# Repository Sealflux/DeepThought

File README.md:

# DeepThought
A pocket keychain that displays DeepSeek quotes on an OLED at the push of a button. 
Powered by a Seeed XIAO ESP32-C3
## Built for Horizons Polaris Hack Club
## Features
- Press button to cycle through DeepSeek quotes
- 128x64 OLED Display
- Compact keychain(slay!!)
- Rechargable LiPo Battery

## Hardware
- Seeed Xiao ESP32-C3
- SSD1306 128x64 OLED (I2C)
- Tactile Push Button
- 250mAh LiPo Battery
- 3D-printed case

## BOM
| Part | Quantity | Cost | Link
|------|-----|------|------|
| Seeed Xiao ESP32-C3 | 1 | $6.35 | https://www.seeedstudio.com/Seeed-XIAO-ESP32C3-p-5431.html |
| SSD1306 0.96" OLED | 1 | $2.24 | https://www.lcsc.com/product-detail/C5248080.html |
| Tactile Push Button | 50 | $0.56 | https://www.lcsc.com/product-detail/C2888493.html |
| LiPo 250mAh | 1 | $9.95 | https://www.amazon.com/EEMB-Battery-Rechargeable-Lithium-Connector/dp/B08FD3V6TF |
| PCB Board | 5 | $2.10 | https://www.jlcpcb.com | 
| Shipping | 1 | $52.39 | $6.20(Seeed) + $11.33(LCSC) + $6.99(Amazon) + $27.87(JLCPCB) |

## Steps To Reproduce

1. Order PCB from JLCPCB, uploading the gerbers.zip in the production folder.
2. 3D print the case using the Bottom and Top stl in the production folder.
3. Order parts using the BOM links above.
4. Solder the parts from the BOM links above to the PCB.
5. Connect the LiPo battery to the battery pads of the PCB(its at the top)
6. Flash the firmware using Arduino IDE in the firmware folder.
7. Assemble the case using super glue, sand down the edges first for better connection.
8. Use Deepthought by pressing the button!

## Firmware/Programming
### Steps to connect/use replicate/mirror the official Seeed website: https://wiki.seeedstudio.com XIAO_ESP32C3_Getting_Started/

1. Connect XIAO ESP32C3 to your computer via a USB Type-C cable.
2. Donwload and Install Arduino IDE
3. Add ESP32 board package to your Arduino IDE
4. Intall Adafruit SSD1306 and Adafruit GFX libraries
5. Download the code from the firmware folder and open it or copy and paste it into the IDE!
5. Select the board
6. Upload the code

## Schematic

## PCB

## PCBA

## Case

## Photos of real thing if I actually can afford grant from horizons(probably not, please polaris!)

## Demo Video

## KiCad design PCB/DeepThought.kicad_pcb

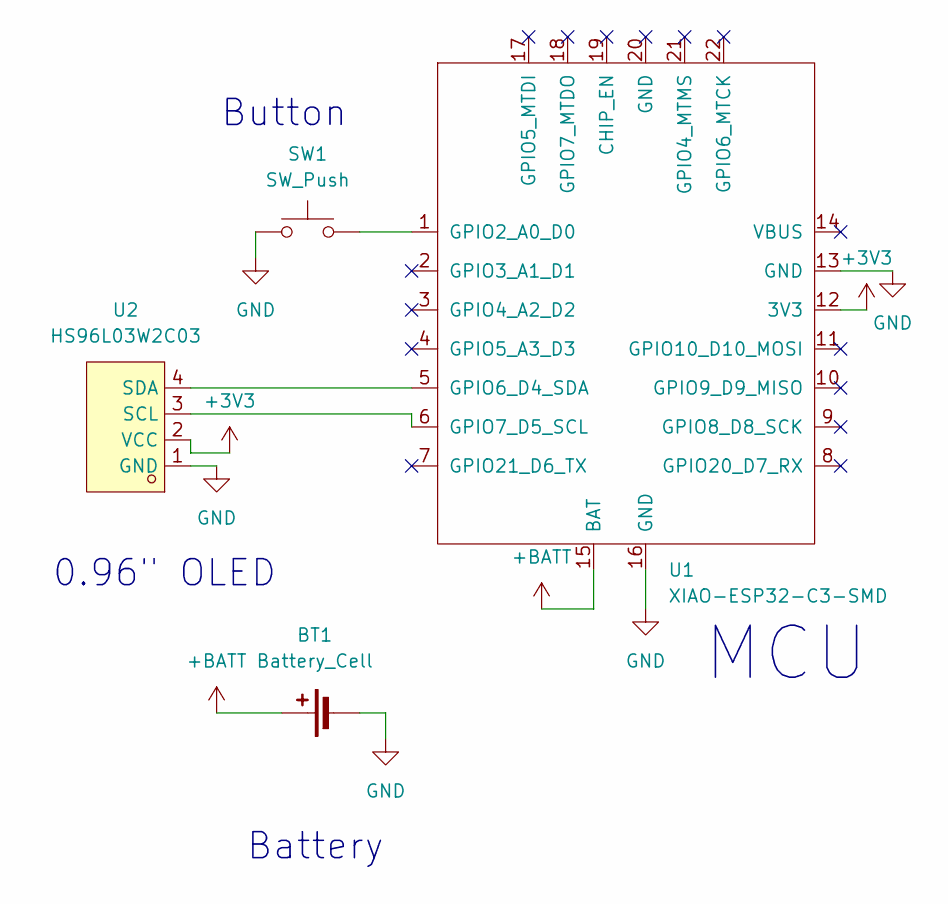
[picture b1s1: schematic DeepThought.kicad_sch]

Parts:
BT1: Battery_Cell; PinHeader_1x02_P2.54mm_Vertical
SW1: SW_Push; SW-TH_4P-L4.5-W4.5-P3.00-LS4.8
U1: XIAO-ESP32-C3-SMD; XIAO-ESP32-C3-DIP-SMD
U2: HS96L03W2C03; OLED-TH_L27.8-W27.2-P2.54_C9900033791; MPN HS96L03W2C03; LCSC Part C5248080

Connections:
+3V3: U1.12 (3V3), U2.2 (VCC)
+BATT: BT1.1 (+), U1.15 (BAT)
GND: BT1.2 (-), SW1.1, U1.13 (GND), U1.16 (GND), U2.1 (GND)
unnamed: SW1.2, U1.1 (GPIO2_A0_D0)
unnamed: U1.5 (GPIO6_D4_SDA), U2.4 (SDA)
unnamed: U1.6 (GPIO7_D5_SCL), U2.3 (SCL)

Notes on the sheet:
MCU
Button
0.96" OLED
Battery

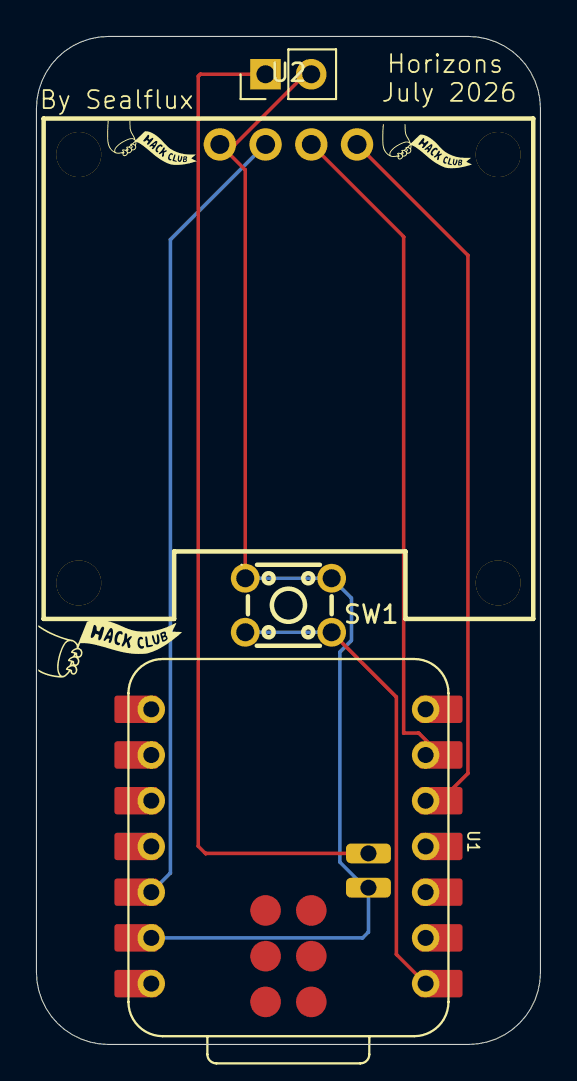
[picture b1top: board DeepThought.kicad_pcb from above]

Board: 2 copper layers, 28.0 x 56.0 mm, 4 parts (0 on the bottom side), 6 nets.
